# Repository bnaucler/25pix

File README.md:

# 25pix game console
A simple game console with a 25 pixel 'screen' built of WS2812 LEDs

## Created by
Björn Westerberg Nauclér (mail@bnaucler.se) 2022

## Installation
The software is created with [PlatformIO](https://platformio.org) core and can be installed with `pio run -t upload`  
Edit `platformio.ini` to set upload port

## Software
Configuration can be done by editing macros in `src/25pix_config.h`.  

## Hardware
In the `kicad` sub-directory you can find [KiCad](https://kicad.org) files. If you prefer to send to production as is, the `hw_production` sub-directory has all gerbers, POS/CPL file and BOM in the correct format for ordering from [JLCPCB](https://jlcpcb.com).

## Contributing
Submit an issue or send a pull request if you feel inclined to get involved.

## Disclaimer
This project is in alpha version and, albeit usable, far from polished.  
Feel free to explore (and edit!) the code base, but expect bugs.

## License
MIT (do whatever you want)

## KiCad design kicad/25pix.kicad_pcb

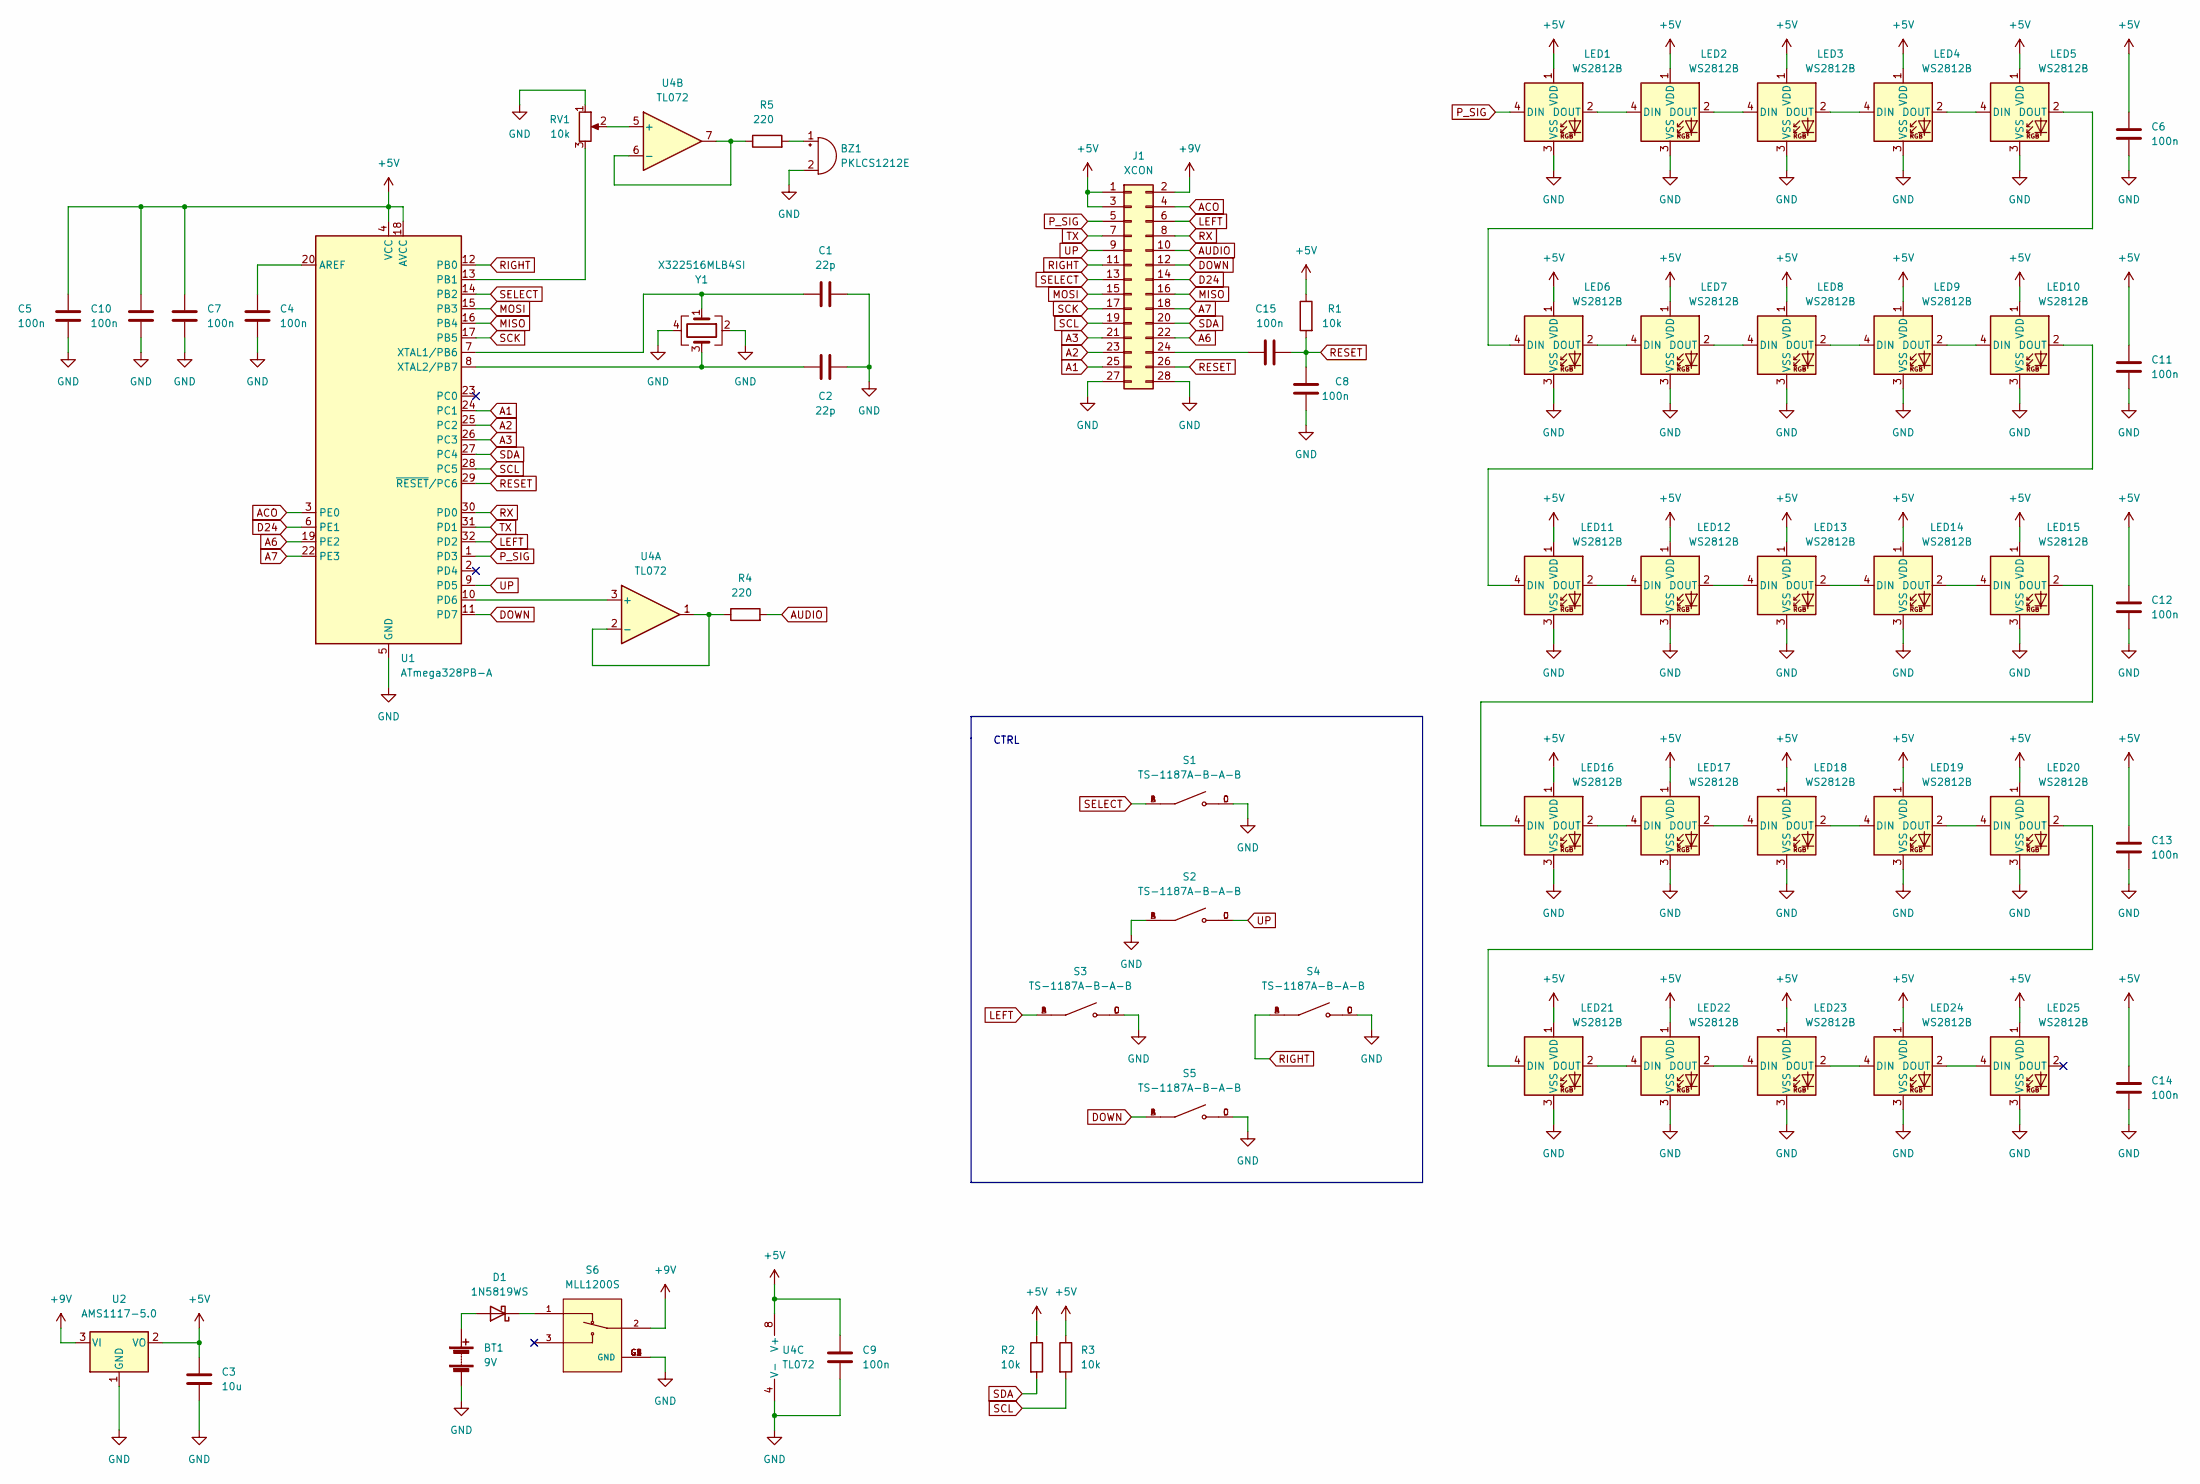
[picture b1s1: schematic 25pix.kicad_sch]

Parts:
BT1: 9V; BatteryHolder_Eagle_12BH611-GR
BZ1: PKLCS1212E; Buzzer_Murata_PKLCS1212E; LCSC C113159
C1, C2: 22p; C_0603_1608Metric
C3: 10u; C_0603_1608Metric
C4, C5, C6, C7, C8, C9, C10, C11, C12, C13, C14, C15: 100n; C_0603_1608Metric
D1: 1N5819WS; D_SOD-323; LCSC C191023
J1: XCON; PinHeader_2x14_P2.54mm_Vertical
LED1: WS2812B; LED_WS2812B_PLCC4_5.0x5.0mm_P3.2mm; LCSC C2843785
LED2, LED3, LED4, LED5, LED6, LED7, LED8, LED9, LED10, LED11, LED12, LED13, LED14, LED15, LED16, LED17, LED18, LED19, LED20, LED21, LED22, LED23, LED24, LED25: WS2812B; LED_WS2812B_PLCC4_5.0x5.0mm_P3.2mm
R1, R2, R3: 10k; R_0603_1608Metric
R4, R5: 220; R_0603_1608Metric
RV1: 10k; Potentiometer_Bourns_3314G_Vertical; LCSC C780220
S1: TS-1187A-B-A-B; SW_TS-1187A-B-A-B; PARTREV A0; LCSC C318884
S2, S3, S4, S5: TS-1187A-B-A-B; SW_TS-1187A-B-A-B; PARTREV A0
S6: MLL1200S; SW_MLL1200S; LCSC C109335
U1: ATmega328PB-A; TQFP-32_7x7mm_P0.8mm; LCSC C132230
U2: AMS1117-5.0; SOT-223-3_TabPin2; LCSC C6187
U4: TL072; SOIC-8_3.9x4.9mm_P1.27mm; LCSC C6961
Y1: X322516MLB4SI; Crystal_SMD_3225-4Pin_3.2x2.5mm; LCSC C13738

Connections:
+5V: C3.1, C5.1, C6.1, C7.1, C9.1, C10.1, C11.1, C12.1, C13.1, C14.1, J1.1, J1.3, LED1.1 (VDD), LED2.1 (VDD), LED3.1 (VDD), LED4.1 (VDD), LED5.1 (VDD), LED6.1 (VDD), LED7.1 (VDD), LED8.1 (VDD), LED9.1 (VDD), LED10.1 (VDD), LED11.1 (VDD), LED12.1 (VDD), LED13.1 (VDD), LED14.1 (VDD), LED15.1 (VDD), LED16.1 (VDD), LED17.1 (VDD), LED18.1 (VDD), LED19.1 (VDD), LED20.1 (VDD), LED21.1 (VDD), LED22.1 (VDD), LED23.1 (VDD), LED24.1 (VDD), LED25.1 (VDD), R1.1, R2.1, R3.1, U1.4 (VCC), U1.18 (AVCC), U2.2 (VO), U4.8 (V+)
+9V: J1.2, S6.2, U2.3 (VI)
A1: J1.25, U1.24 (PC1)
A2: J1.23, U1.25 (PC2)
A3: J1.21, U1.26 (PC3)
A6: J1.22, U1.19 (PE2)
A7: J1.18, U1.22 (PE3)
ACO: J1.4, U1.3 (PE0)
AUDIO: J1.10, R4.2
D24: J1.14, U1.6 (PE1)
DOWN: J1.12, S5.A, S5.B, U1.11 (PD7)
GND: BT1.2 (-), BZ1.2 (+), C1.2, C2.2, C3.2, C4.2, C5.2, C6.2, C7.2, C8.2, C9.2, C10.2, C11.2, C12.2, C13.2, C14.2, J1.27, J1.28, LED1.3 (VSS), LED2.3 (VSS), LED3.3 (VSS), LED4.3 (VSS), LED5.3 (VSS), LED6.3 (VSS), LED7.3 (VSS), LED8.3 (VSS), LED9.3 (VSS), LED10.3 (VSS), LED11.3 (VSS), LED12.3 (VSS), LED13.3 (VSS), LED14.3 (VSS), LED15.3 (VSS), LED16.3 (VSS), LED17.3 (VSS), LED18.3 (VSS), LED19.3 (VSS), LED20.3 (VSS), LED21.3 (VSS), LED22.3 (VSS), LED23.3 (VSS), LED24.3 (VSS), LED25.3 (VSS), RV1.1, S1.C, S1.D, S2.A, S2.B, S3.C, S3.D, S4.C, S4.D, S5.C, S5.D, S6.G1 (GND), S6.G2 (GND), S6.G3 (GND), S6.G4 (GND), U1.5 (GND), U1.21 (GND), U2.1 (GND), U4.4 (V-), Y1.2, Y1.4
LEFT: J1.6, S3.A, S3.B, U1.32 (PD2)
MISO: J1.16, U1.16 (PB4)
MOSI: J1.15, U1.15 (PB3)
unnamed: BT1.1 (+), D1.2 (A)
unnamed: BZ1.1 (-), R5.2
unnamed: C1.1, U1.7 (XTAL1/PB6), Y1.1
unnamed: C2.1, U1.8 (XTAL2/PB7), Y1.3
unnamed: C4.1, U1.20 (AREF)
unnamed: C15.1, J1.24
unnamed: D1.1 (K), S6.1
unnamed: LED1.2 (DOUT), LED2.4 (DIN)
unnamed: LED2.2 (DOUT), LED3.4 (DIN)
unnamed: LED3.2 (DOUT), LED4.4 (DIN)
unnamed: LED4.2 (DOUT), LED5.4 (DIN)
unnamed: LED5.2 (DOUT), LED6.4 (DIN)
unnamed: LED6.2 (DOUT), LED7.4 (DIN)
unnamed: LED7.2 (DOUT), LED8.4 (DIN)
unnamed: LED8.2 (DOUT), LED9.4 (DIN)
unnamed: LED10.2 (DOUT), LED11.4 (DIN)
unnamed: LED9.2 (DOUT), LED10.4 (DIN)
unnamed: LED11.2 (DOUT), LED12.4 (DIN)
unnamed: LED12.2 (DOUT), LED13.4 (DIN)
unnamed: LED13.2 (DOUT), LED14.4 (DIN)
unnamed: LED14.2 (DOUT), LED15.4 (DIN)
unnamed: LED15.2 (DOUT), LED16.4 (DIN)
unnamed: LED16.2 (DOUT), LED17.4 (DIN)
unnamed: LED17.2 (DOUT), LED18.4 (DIN)
unnamed: LED18.2 (DOUT), LED19.4 (DIN)
unnamed: LED19.2 (DOUT), LED20.4 (DIN)
unnamed: LED20.2 (DOUT), LED21.4 (DIN)
unnamed: LED21.2 (DOUT), LED22.4 (DIN)
unnamed: LED22.2 (DOUT), LED23.4 (DIN)
unnamed: LED23.2 (DOUT), LED24.4 (DIN)
unnamed: LED24.2 (DOUT), LED25.4 (DIN)
unnamed: R4.1, U4.1, U4.2 (-)
unnamed: R5.1, U4.6 (-), U4.7
unnamed: RV1.2, U4.5 (+)
unnamed: RV1.3, U1.13 (PB1)
unnamed: U1.10 (PD6), U4.3 (+)
P_SIG: J1.5, LED1.4 (DIN), U1.1 (PD3)
RESET: C8.1, C15.2, J1.26, R1.2, U1.29 (~RESET/PC6)
RIGHT: J1.11, S4.A, S4.B, U1.12 (PB0)
RX: J1.8, U1.30 (PD0)
SCK: J1.17, U1.17 (PB5)
SCL: J1.19, R3.2, U1.28 (PC5)
SDA: J1.20, R2.2, U1.27 (PC4)
SELECT: J1.13, S1.A, S1.B, U1.14 (PB2)
TX: J1.7, U1.31 (PD1)
UP: J1.9, S2.C, S2.D, U1.9 (PD5)

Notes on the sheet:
CTRL

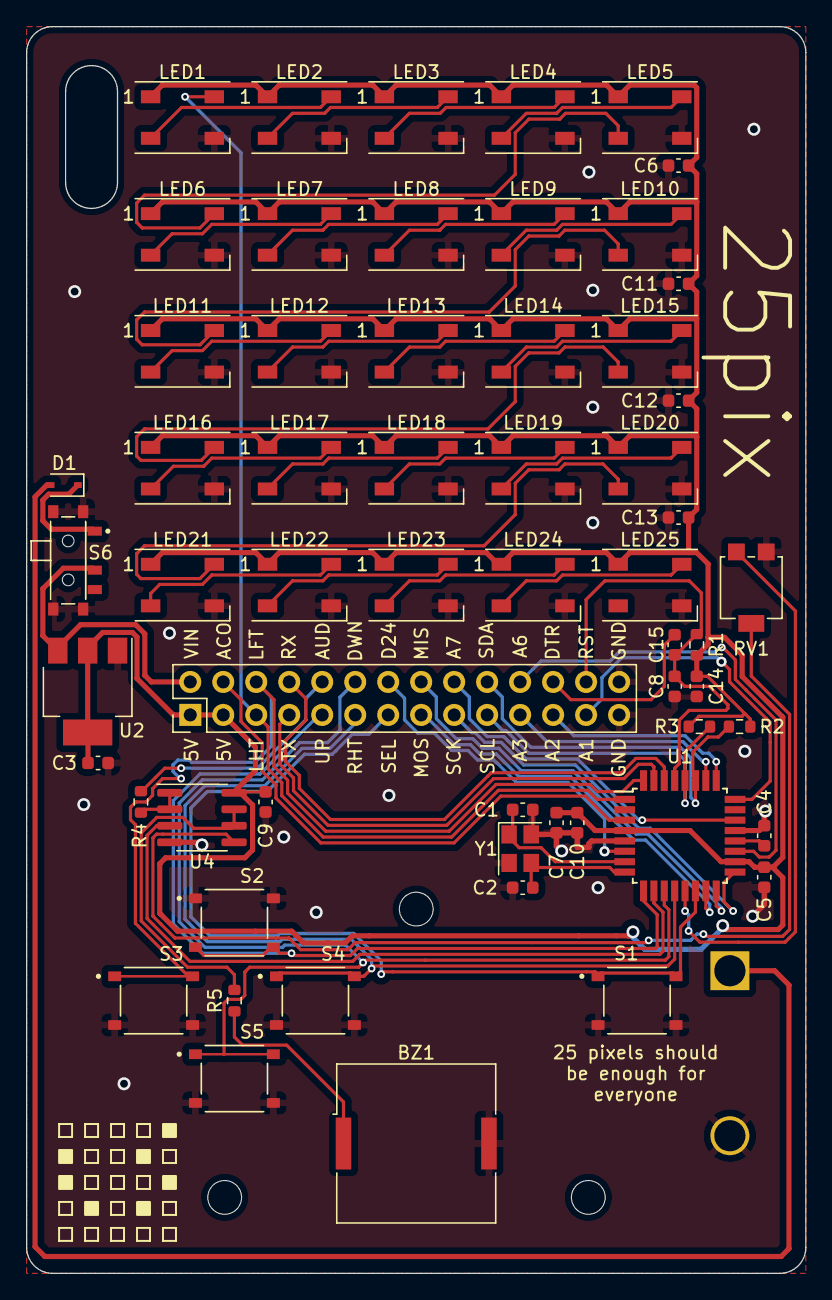
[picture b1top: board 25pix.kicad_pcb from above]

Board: 2 copper layers, 60.0 x 96.0 mm, 60 parts (1 on the bottom side), 61 nets.

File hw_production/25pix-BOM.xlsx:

25pix
Comment | Designator | Footprint | LCSC Part Number
PKLCS1212E | BZ1 | Buzzer_Beeper:Buzzer_Murata_PKLCS1212E | C113159
22p | C1,C2 | Capacitor_SMD:C_0603_1608Metric | C1653
10u | C3 | Capacitor_SMD:C_0603_1608Metric | C96446
100n | C4,C5,C6,C7,C8,C9,C10,C11,C12,C13,C14,C15 | Capacitor_SMD:C_0603_1608Metric | C14663
1N5819WS | D1 | Diode_SMD:D_SOD-323 | C191023
WS2812B | LED1,LED2,LED3,LED4,LED5,LED6,LED7,LED8,LED9,LED10,LED11,LED12,LED13,LED14,LED1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 | LED_SMD:LED_WS2812B_PLCC4_5.0x5.0mm_P3.2mm | C2843785
10k | R1,R2,R3 | Resistor_SMD:R_0603_1608Metric | C25804
220 | R4,R5 | Resistor_SMD:R_0603_1608Metric | C22962
10k | RV1 | Potentiometer_SMD:Potentiometer_Bourns_3314G_Vertical | C780220
TS-1187A-B-A-B | S1,S2,S3,S4,S5 | SMD | C318884
SSSS811101 | S6 | SMD | C109335
ATmega328PB-A | U1 | Package_QFP:TQFP-32_7x7mm_P0.8mm | C132230
AMS1117-5.0 | U2 | Package_TO_SOT_SMD:SOT-223-3_TabPin2 | C6187
TL072 | U4 | Package_SO:SOIC-8_3.9x4.9mm_P1.27mm | C6961
X322516MLB4SI | Y1 | Crystal:Crystal_SMD_3225-4Pin_3.2x2.5mm | C13738

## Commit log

2022-12-10 Updating README with production info
2022-12-10 Including image in README

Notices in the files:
kicad/25pix.kicad_pcb:
CC0 - public domain
